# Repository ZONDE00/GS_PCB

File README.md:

# GS_PCB
Ground station PCB design files

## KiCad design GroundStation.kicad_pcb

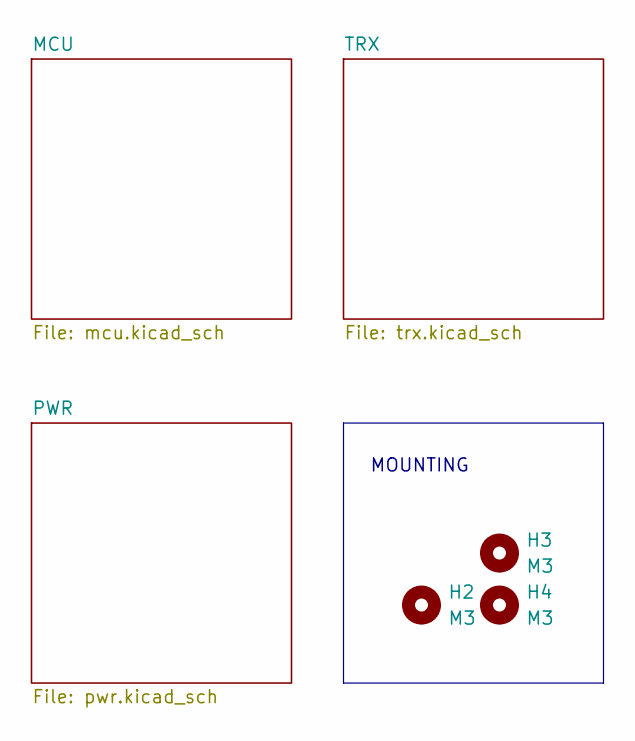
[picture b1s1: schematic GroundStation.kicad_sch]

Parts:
H2, H3, H4: M3; MountingHole_3mm

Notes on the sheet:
MOUNTING

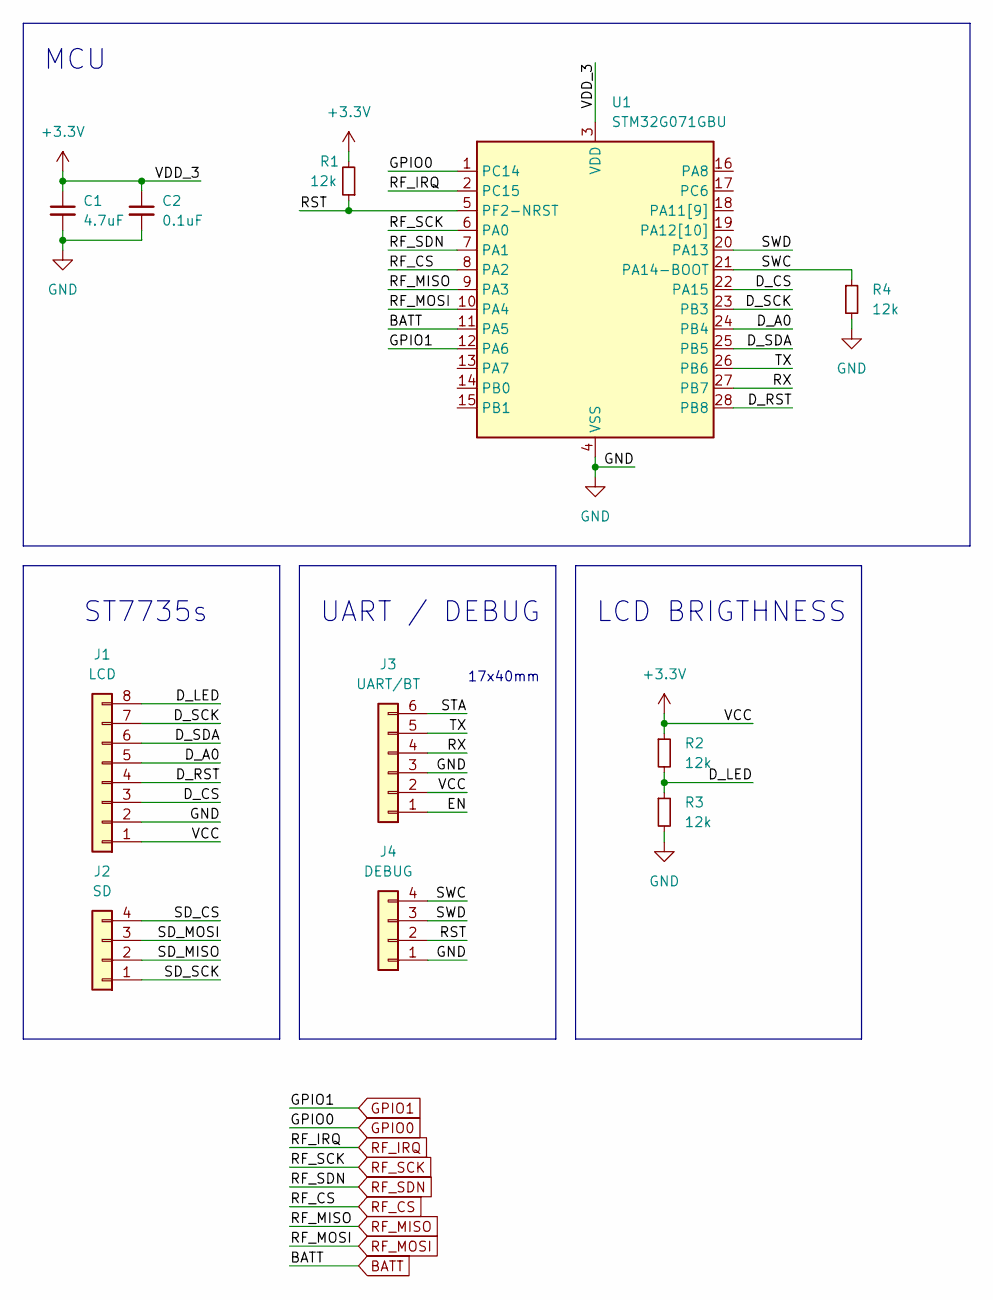
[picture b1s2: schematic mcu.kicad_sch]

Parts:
C1: 4.7uF; C_0603_1608Metric
C2: 0.1uF; C_0402_1005Metric
J1: LCD; PinSocket_1x08_P2.54mm_Vertical
J2: SD; PinSocket_1x04_P2.54mm_Vertical
J3: UART/BT; PinSocket_1x06_P2.54mm_Horizontal
J4: DEBUG; PinSocket_1x04_P2.54mm_Horizontal
R1, R2, R3, R4: 12k; R_0402_1005Metric
U1: STM32G071GBU; QFN-28_4x4mm_P0.5mm

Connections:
+3V3: C1.1, C2.1, J1.1, J3.2, R1.2, R2.1, U1.3 (VDD); also elsewhere on the board
/MCU/D_A0: J1.5, U1.24 (PB4)
/MCU/D_CS: J1.3, U1.22 (PA15)
/MCU/D_LED: J1.8, R2.2, R3.1
/MCU/D_RST: J1.4, U1.28 (PB8)
/MCU/D_SCK: J1.7, U1.23 (PB3)
/MCU/D_SDA: J1.6, U1.25 (PB5)
/MCU/EN: J3.1
/MCU/RST: J4.2, R1.1, U1.5 (PF2-NRST)
/MCU/RX: J3.4, U1.27 (PB7)
/MCU/SD_CS: J2.4
/MCU/SD_MISO: J2.2
/MCU/SD_MOSI: J2.3
/MCU/SD_SCK: J2.1
/MCU/STA: J3.6
/MCU/SWC: J4.4, R4.1, U1.21 (PA14-BOOT)
/MCU/SWD: J4.3, U1.20 (PA13)
/MCU/TX: J3.5, U1.26 (PB6)
BATT: U1.11 (PA5); also elsewhere on the board
GND: C1.2, C2.2, J1.2, J3.3, J4.1, R3.2, R4.2, U1.4 (VSS); also elsewhere on the board
GPIO0: U1.1 (PC14); also elsewhere on the board
GPIO1: U1.12 (PA6); also elsewhere on the board
RF_CS: U1.8 (PA2); also elsewhere on the board
RF_IRQ: U1.2 (PC15); also elsewhere on the board
RF_MISO: U1.9 (PA3); also elsewhere on the board
RF_MOSI: U1.10 (PA4); also elsewhere on the board
RF_SCK: U1.6 (PA0); also elsewhere on the board
RF_SDN: U1.7 (PA1); also elsewhere on the board

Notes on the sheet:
MCU
LCD BRIGTHNESS
UART / DEBUG
ST7735s
17x40mm

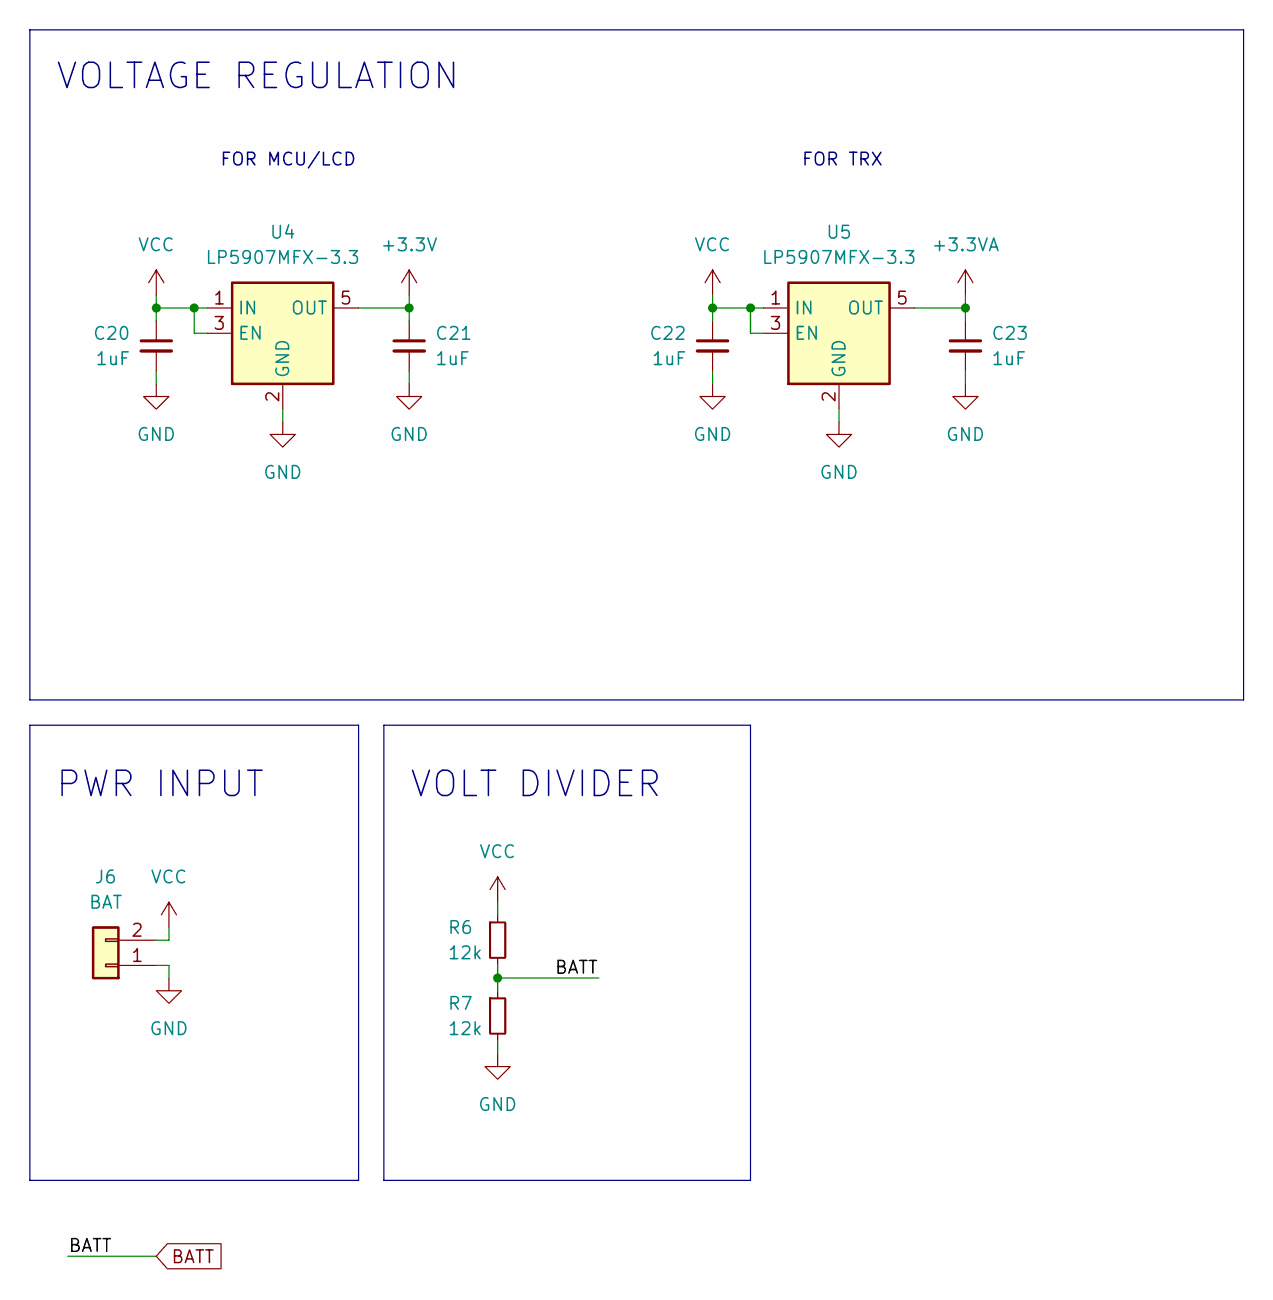
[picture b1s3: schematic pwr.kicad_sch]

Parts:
C20, C21, C22, C23: 1uF; C_0603_1608Metric
J6: BAT; PinHeader_1x02_P2.54mm_Vertical
R6, R7: 12k; LED_0402_1005Metric
U4, U5: LP5907MFX-3.3; SOT-23-5

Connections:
+3.3VA: C23.1, U5.5 (OUT); also elsewhere on the board
+3V3: C21.1, U4.5 (OUT); also elsewhere on the board
BATT: R6.2, R7.1; also elsewhere on the board
GND: C20.2, C21.2, C22.2, C23.2, J6.1, R7.2, U4.2 (GND), U5.2 (GND); also elsewhere on the board
VCC: C20.1, C22.1, J6.2, R6.1, U4.1 (IN), U4.3 (EN), U5.1 (IN), U5.3 (EN)

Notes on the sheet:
FOR MCU/LCD
FOR TRX
PWR INPUT
VOLTAGE REGULATION
VOLT DIVIDER

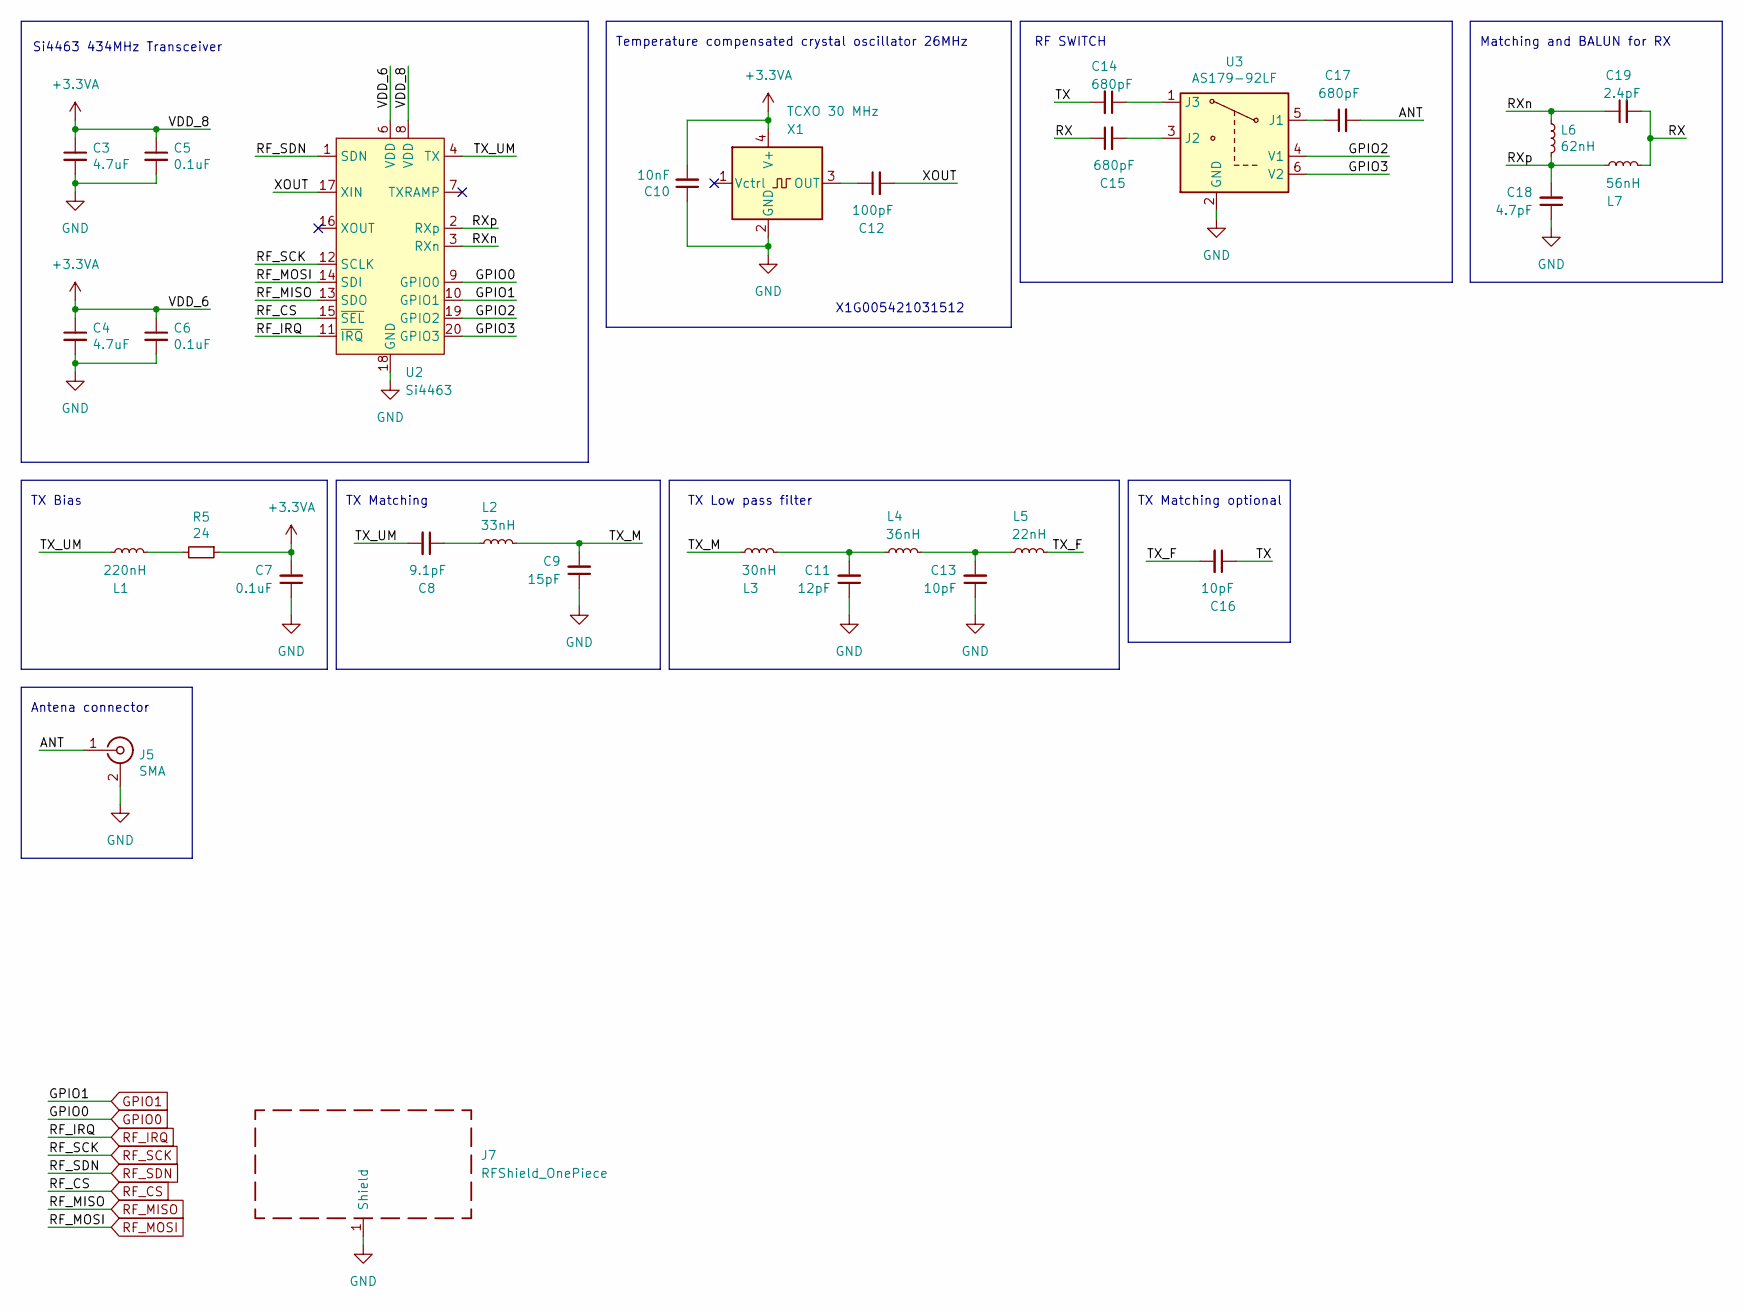
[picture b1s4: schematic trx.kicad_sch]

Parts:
C3, C4: 4.7uF; C_0603_1608Metric
C5, C6, C7: 0.1uF; C_0402_1005Metric
C8: 9.1pF; C_0402_1005Metric
C9: 15pF; C_0402_1005Metric
C10: 10nF; C_0402_1005Metric
C11: 12pF; C_0402_1005Metric
C12: 100pF; C_0402_1005Metric
C13, C16: 10pF; C_0402_1005Metric
C14, C15, C17: 680pF; C_0402_1005Metric
C18: 4.7pF; C_0402_1005Metric
C19: 2.4pF; C_0402_1005Metric
J5: SMA; SMA_Molex_73251-1153_EdgeMount_Horizontal
J7: RFShield_OnePiece; Laird_Technologies_BMI-S-205-F_38.10x25.40mm
L1: 220nH; L_0603_1608Metric
L2: 33nH; L_0402_1005Metric
L3: 30nH; L_0402_1005Metric
L4: 36nH; L_0402_1005Metric
L5: 22nH; L_0402_1005Metric
L6: 62nH; L_0402_1005Metric
L7: 56nH; L_0402_1005Metric
R5: 24; R_0603_1608Metric
U2: Si4463; QFN-20-1EP_4x4mm_P0.5mm_EP2.6x2.6mm_ThermalVias
U3: AS179-92LF; SOT-363_SC-70-6
X1: TCXO 30 MHz; Crystal_SMD_2520-4Pin_2.5x2.0mm

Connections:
+3.3VA: C3.1, C4.1, C5.1, C6.1, C7.2, C10.2, R5.1, U2.6 (VDD), U2.8 (VDD), X1.4 (V+); also elsewhere on the board
/TRX/ANT: C17.2, J5.1 (In)
/TRX/GPIO2: U2.19 (GPIO2), U3.4 (V1)
/TRX/GPIO3: U2.20 (GPIO3), U3.6 (V2)
/TRX/RX: C15.1, C19.2, L7.2
/TRX/RXn: C19.1, L6.1, U2.3 (RXn)
/TRX/RXp: C18.2, L6.2, L7.1, U2.2 (RXp)
/TRX/TX: C14.2, C16.1
/TRX/TX_F: C16.2, L5.2
/TRX/TX_M: C9.2, L2.2, L3.1
/TRX/TX_UM: C8.2, L1.1, U2.4 (TX)
/TRX/XOUT: C12.2, U2.17 (XIN)
GND: C3.2, C4.2, C5.2, C6.2, C7.1, C9.1, C10.1, C11.1, C13.1, C18.1, J5.2 (Ext), J7.1 (Shield), U2.18 (GND), U2.21 (GND), U3.2 (GND), X1.2 (GND); also elsewhere on the board
GPIO0: U2.9 (GPIO0); also elsewhere on the board
GPIO1: U2.10 (GPIO1); also elsewhere on the board
unnamed: C8.1, L2.1
unnamed: C11.2, L3.2, L4.1
unnamed: C12.1, X1.3 (OUT)
unnamed: C13.2, L4.2, L5.1
unnamed: C14.1, U3.1 (J3)
unnamed: C15.2, U3.3 (J2)
unnamed: C17.1, U3.5 (J1)
unnamed: L1.2, R5.2
RF_CS: U2.15 (~SEL); also elsewhere on the board
RF_IRQ: U2.11 (~IRQ); also elsewhere on the board
RF_MISO: U2.13 (SDO); also elsewhere on the board
RF_MOSI: U2.14 (SDI); also elsewhere on the board
RF_SCK: U2.12 (SCLK); also elsewhere on the board
RF_SDN: U2.1 (SDN); also elsewhere on the board

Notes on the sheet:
Si4463 434MHz Transceiver
Temperature compensated crystal oscillator 26MHz
TX Bias
RF SWITCH
Antena connector
TX Low pass filter
Matching and BALUN for RX
X1G005421031512
TX Matching
TX Matching optional

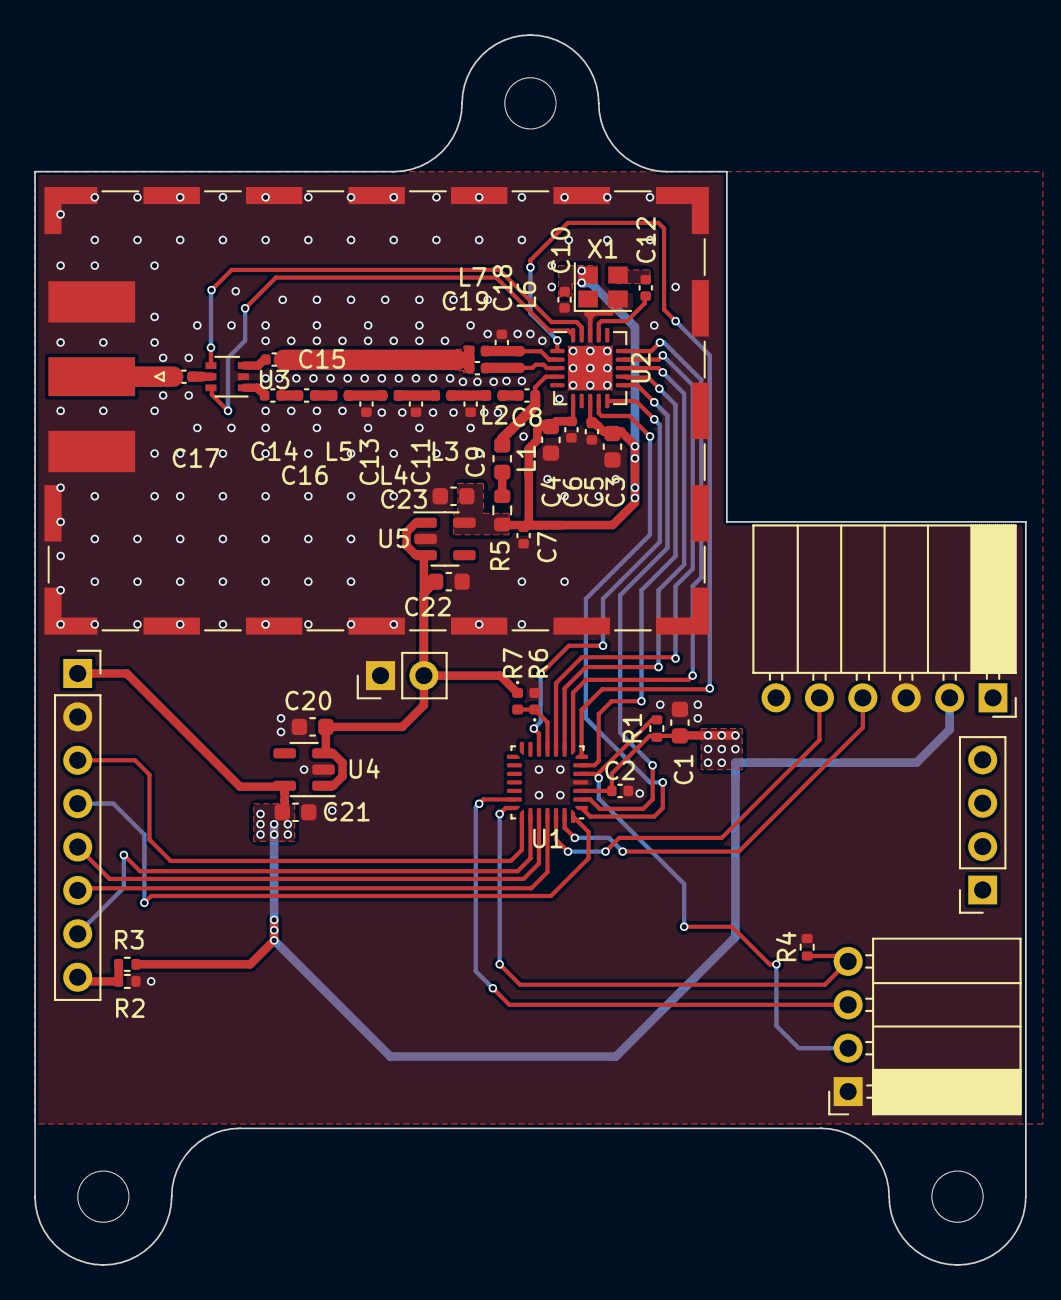
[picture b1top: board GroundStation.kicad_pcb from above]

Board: 2 copper layers, 58.0 x 72.0 mm, 53 parts (0 on the bottom side), 43 nets.

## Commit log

2022-08-13 Init
2022-09-12 First version
2022-11-26 Added project name
